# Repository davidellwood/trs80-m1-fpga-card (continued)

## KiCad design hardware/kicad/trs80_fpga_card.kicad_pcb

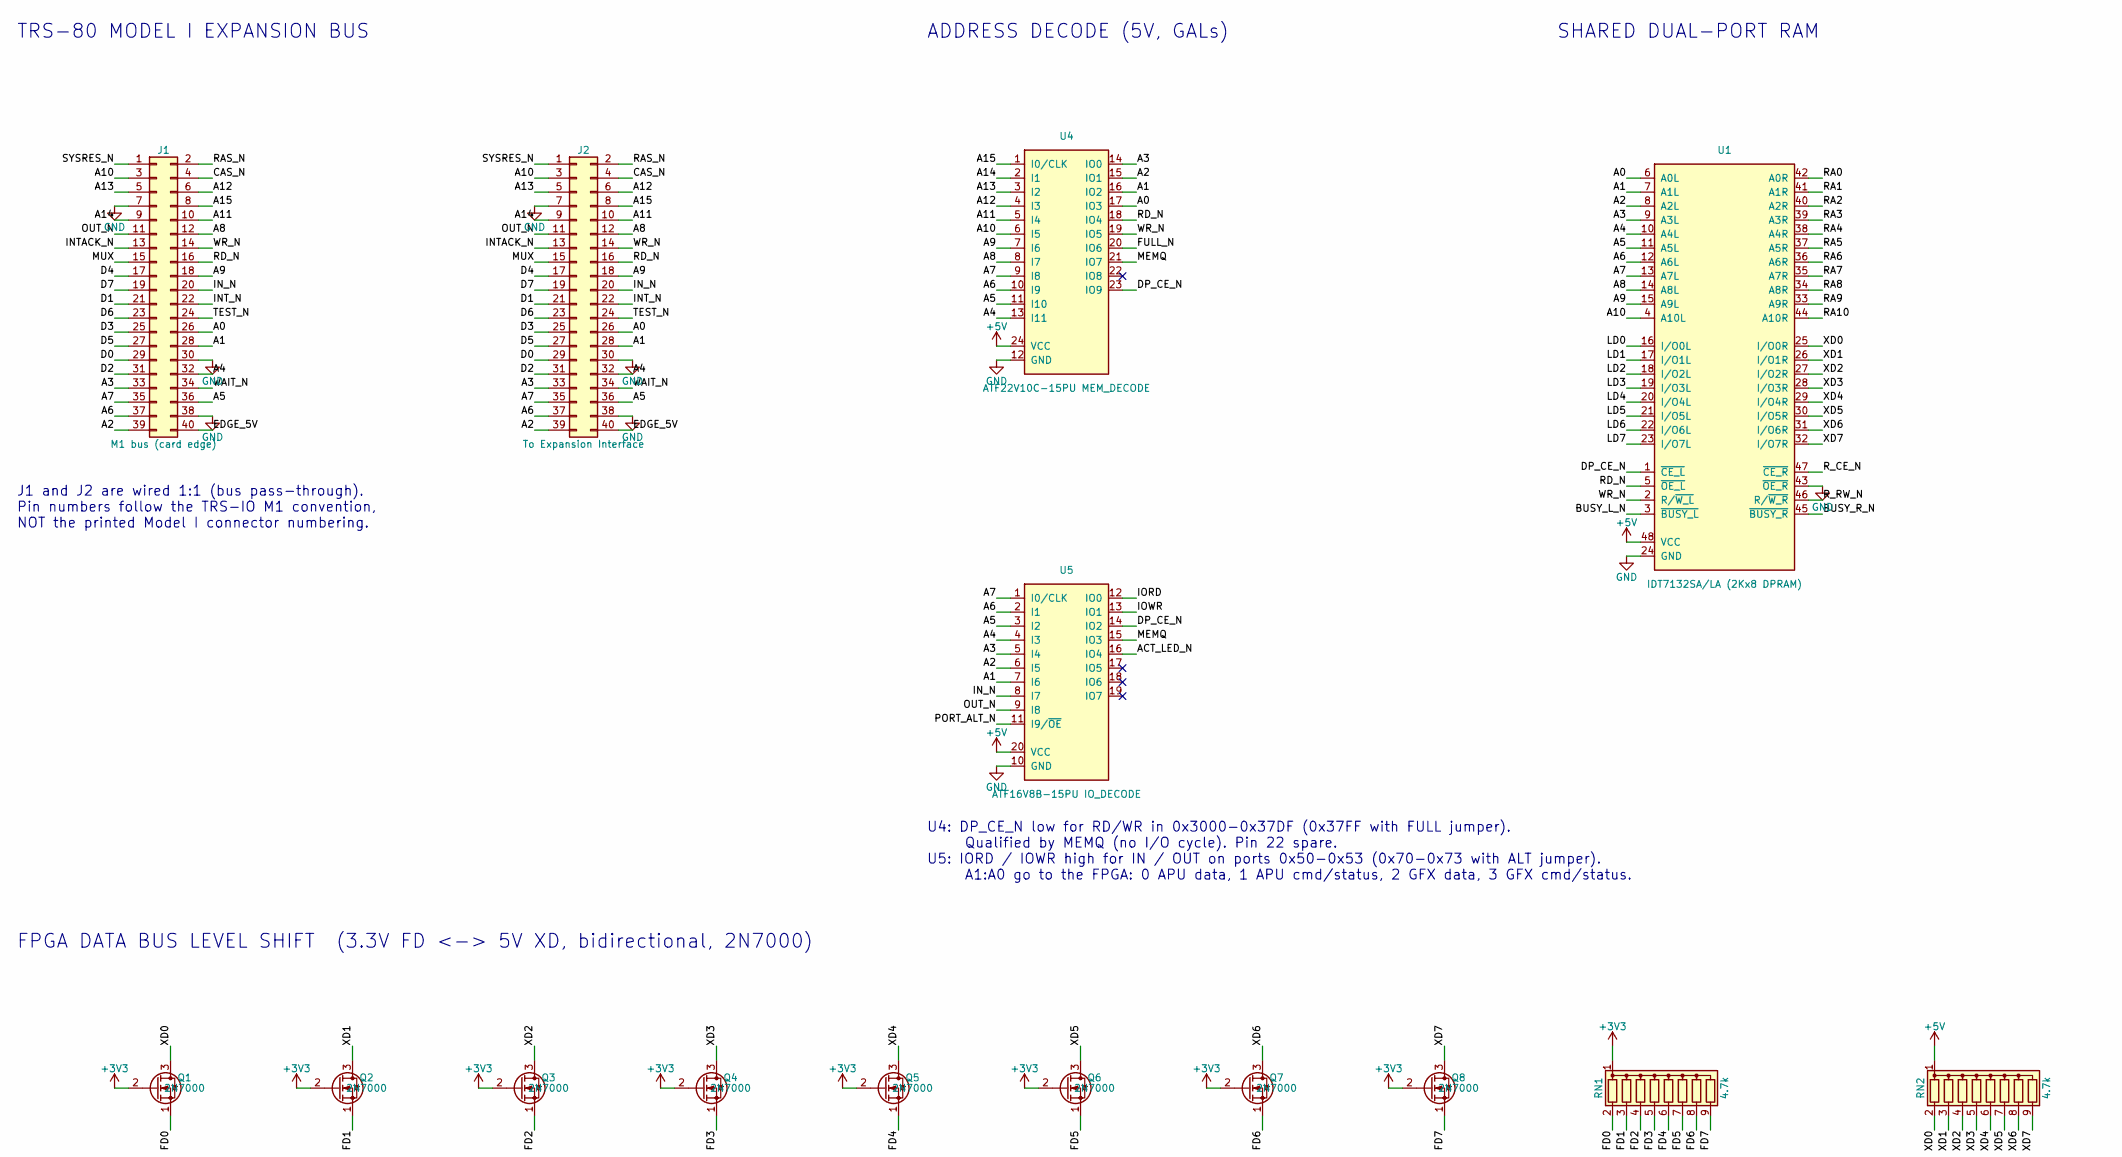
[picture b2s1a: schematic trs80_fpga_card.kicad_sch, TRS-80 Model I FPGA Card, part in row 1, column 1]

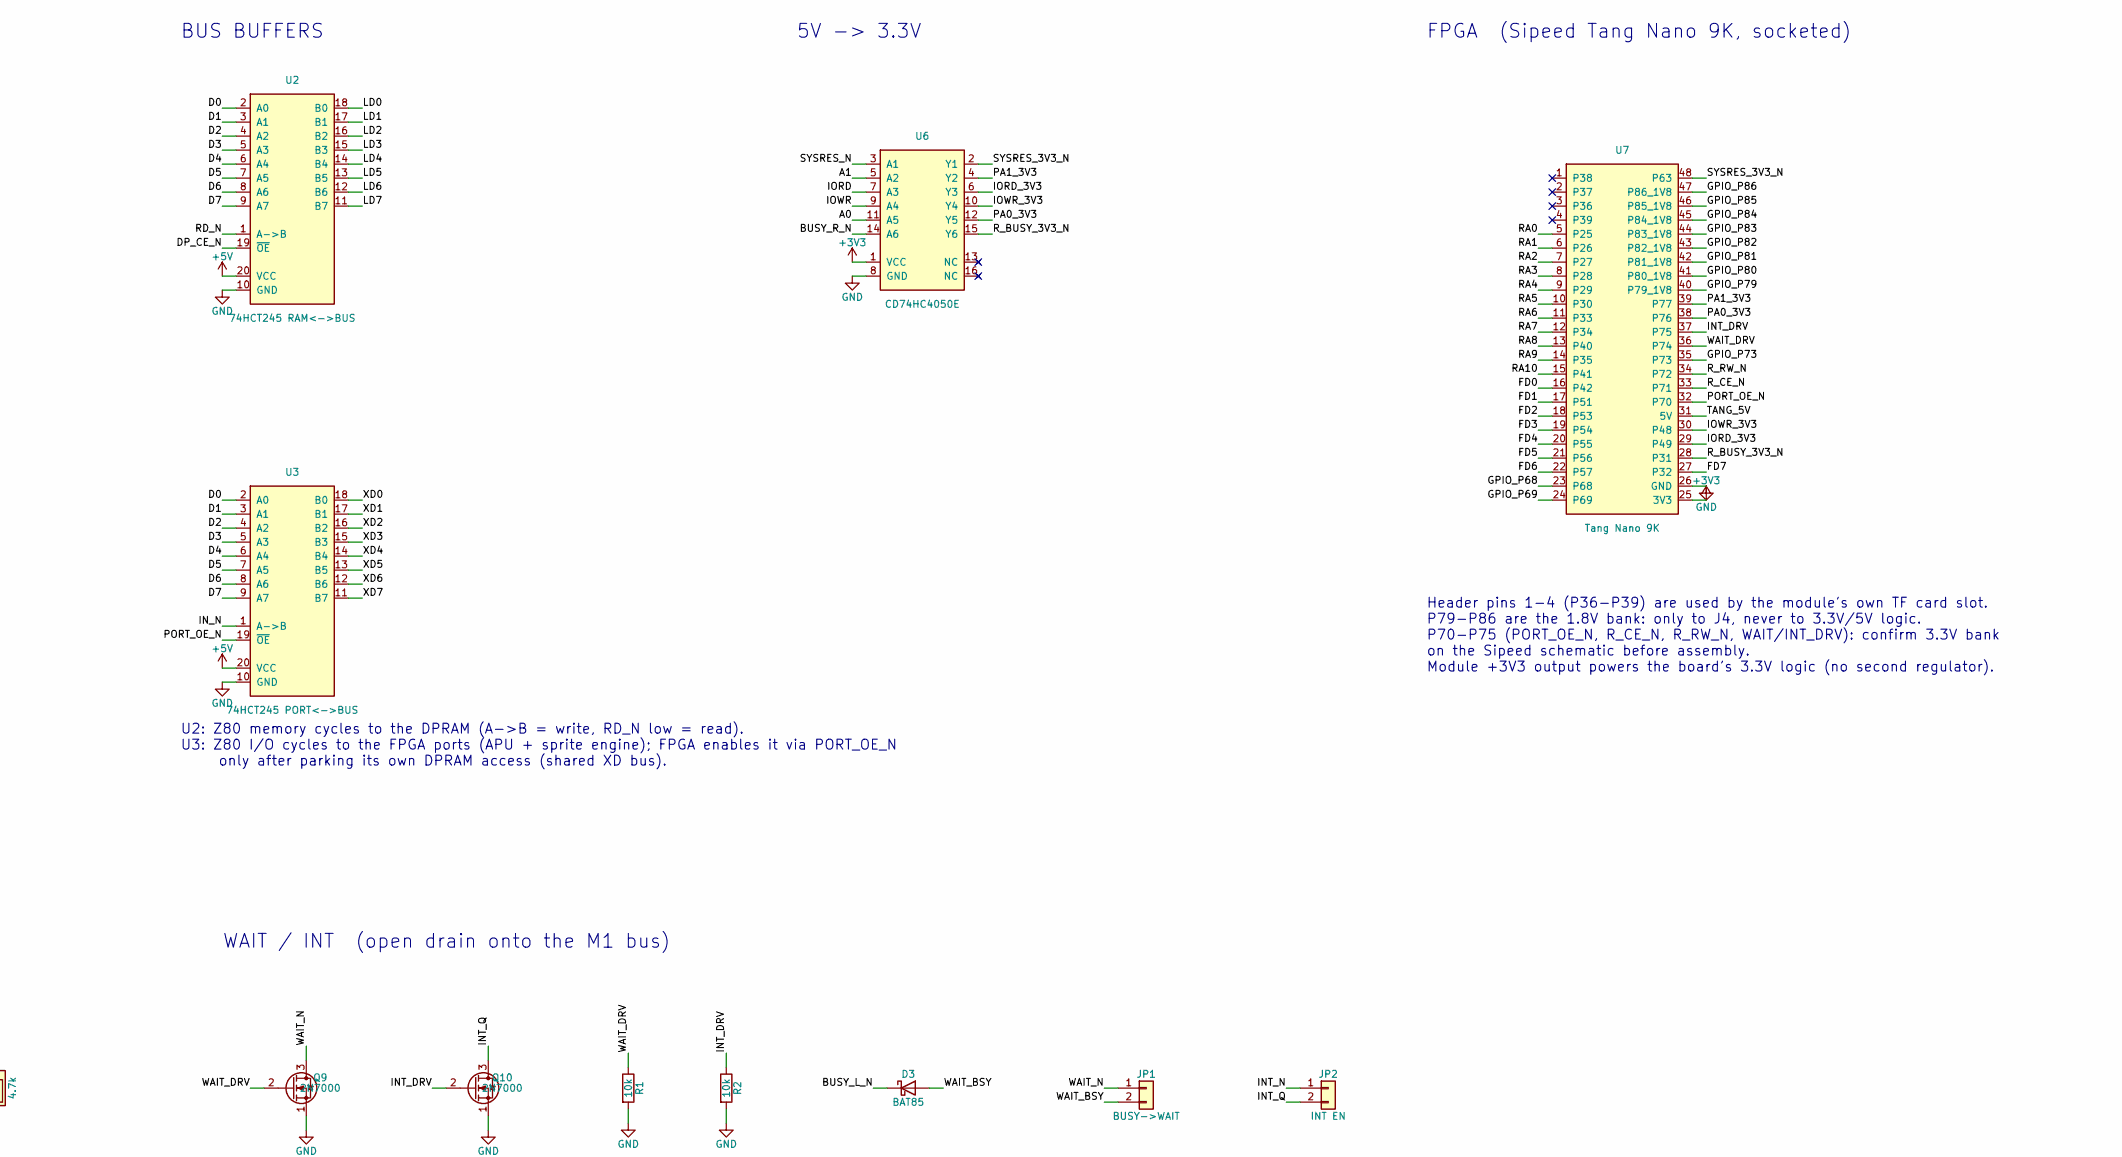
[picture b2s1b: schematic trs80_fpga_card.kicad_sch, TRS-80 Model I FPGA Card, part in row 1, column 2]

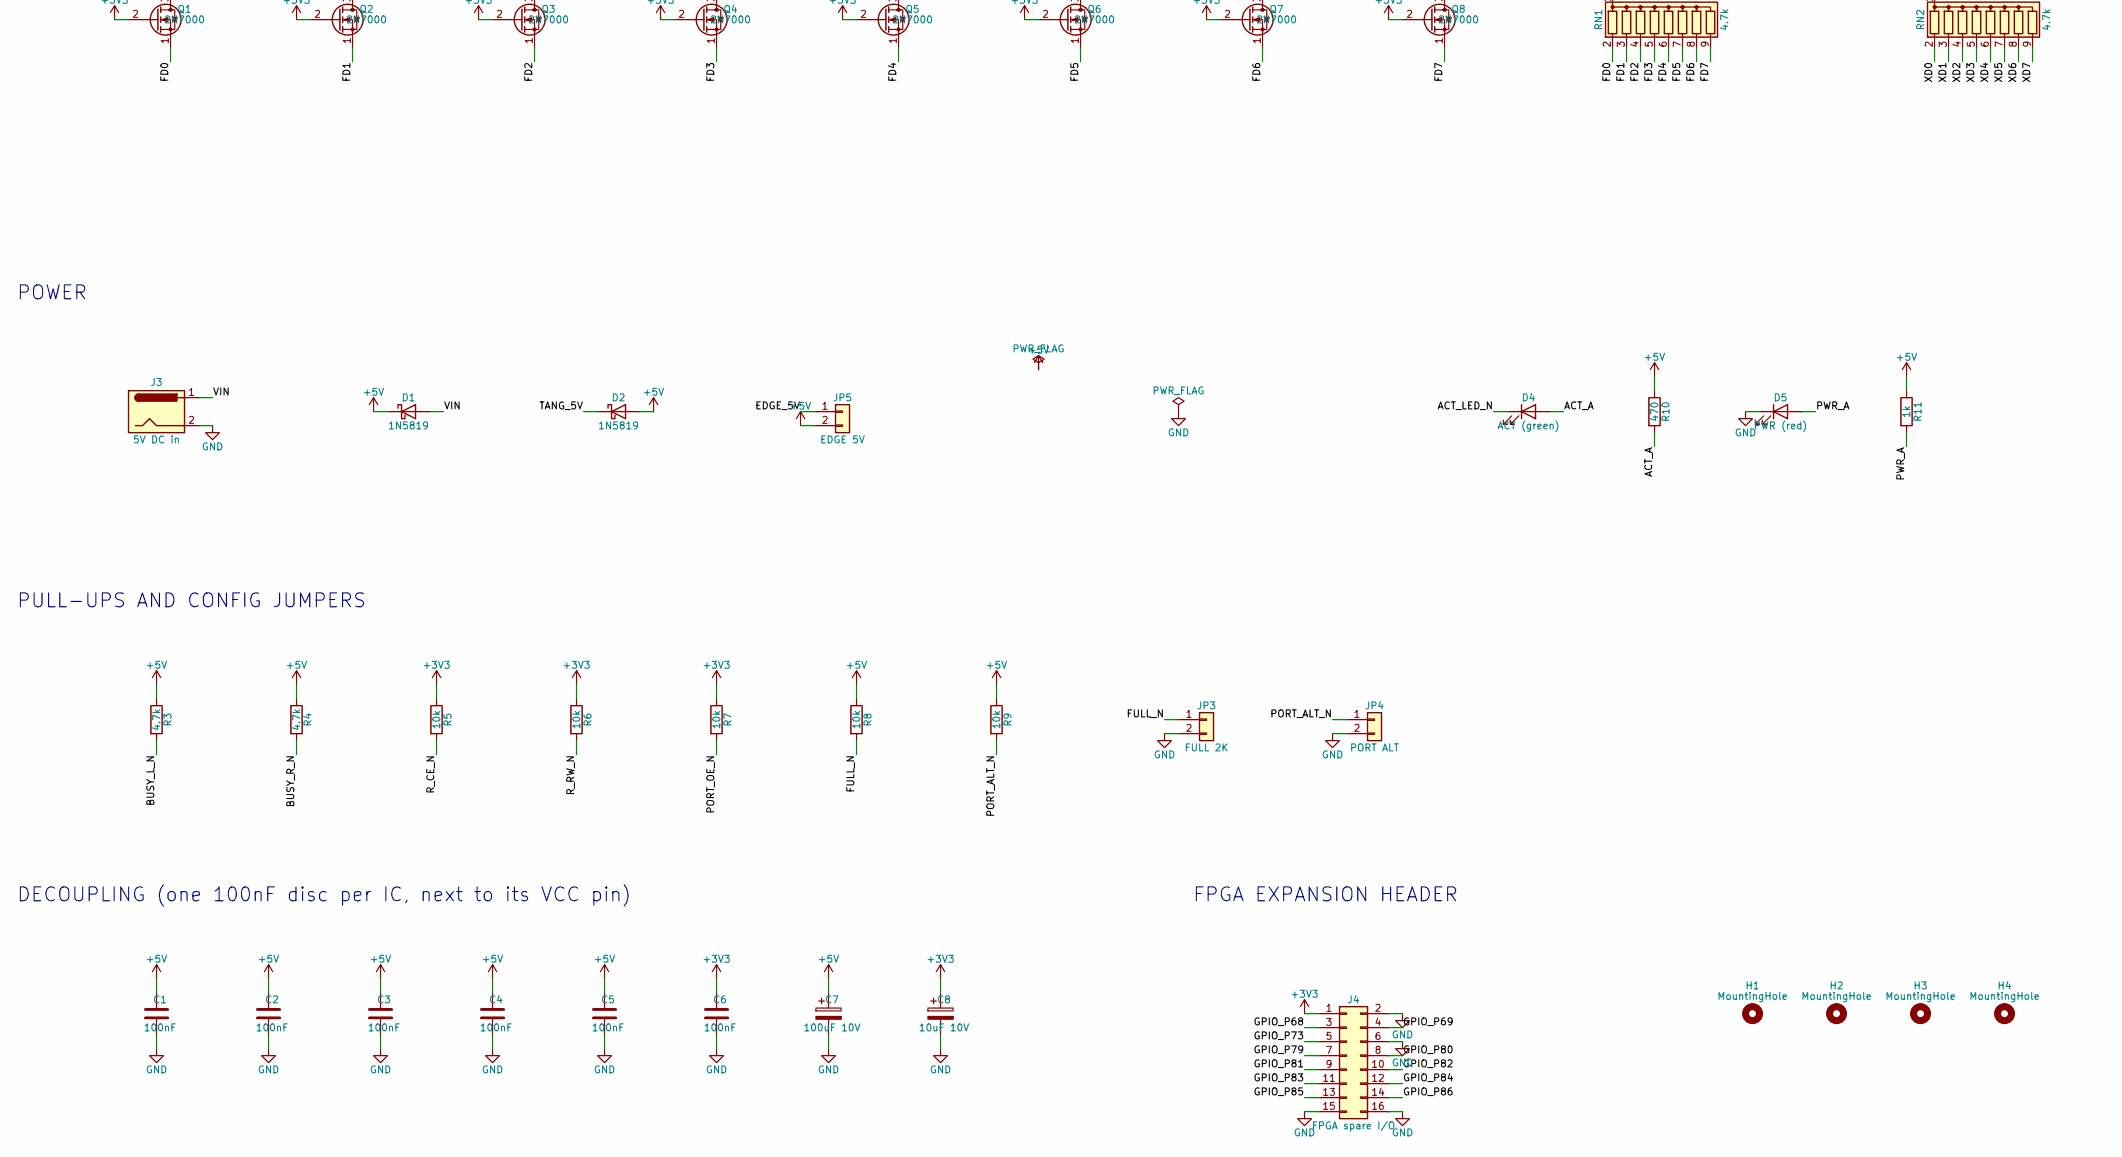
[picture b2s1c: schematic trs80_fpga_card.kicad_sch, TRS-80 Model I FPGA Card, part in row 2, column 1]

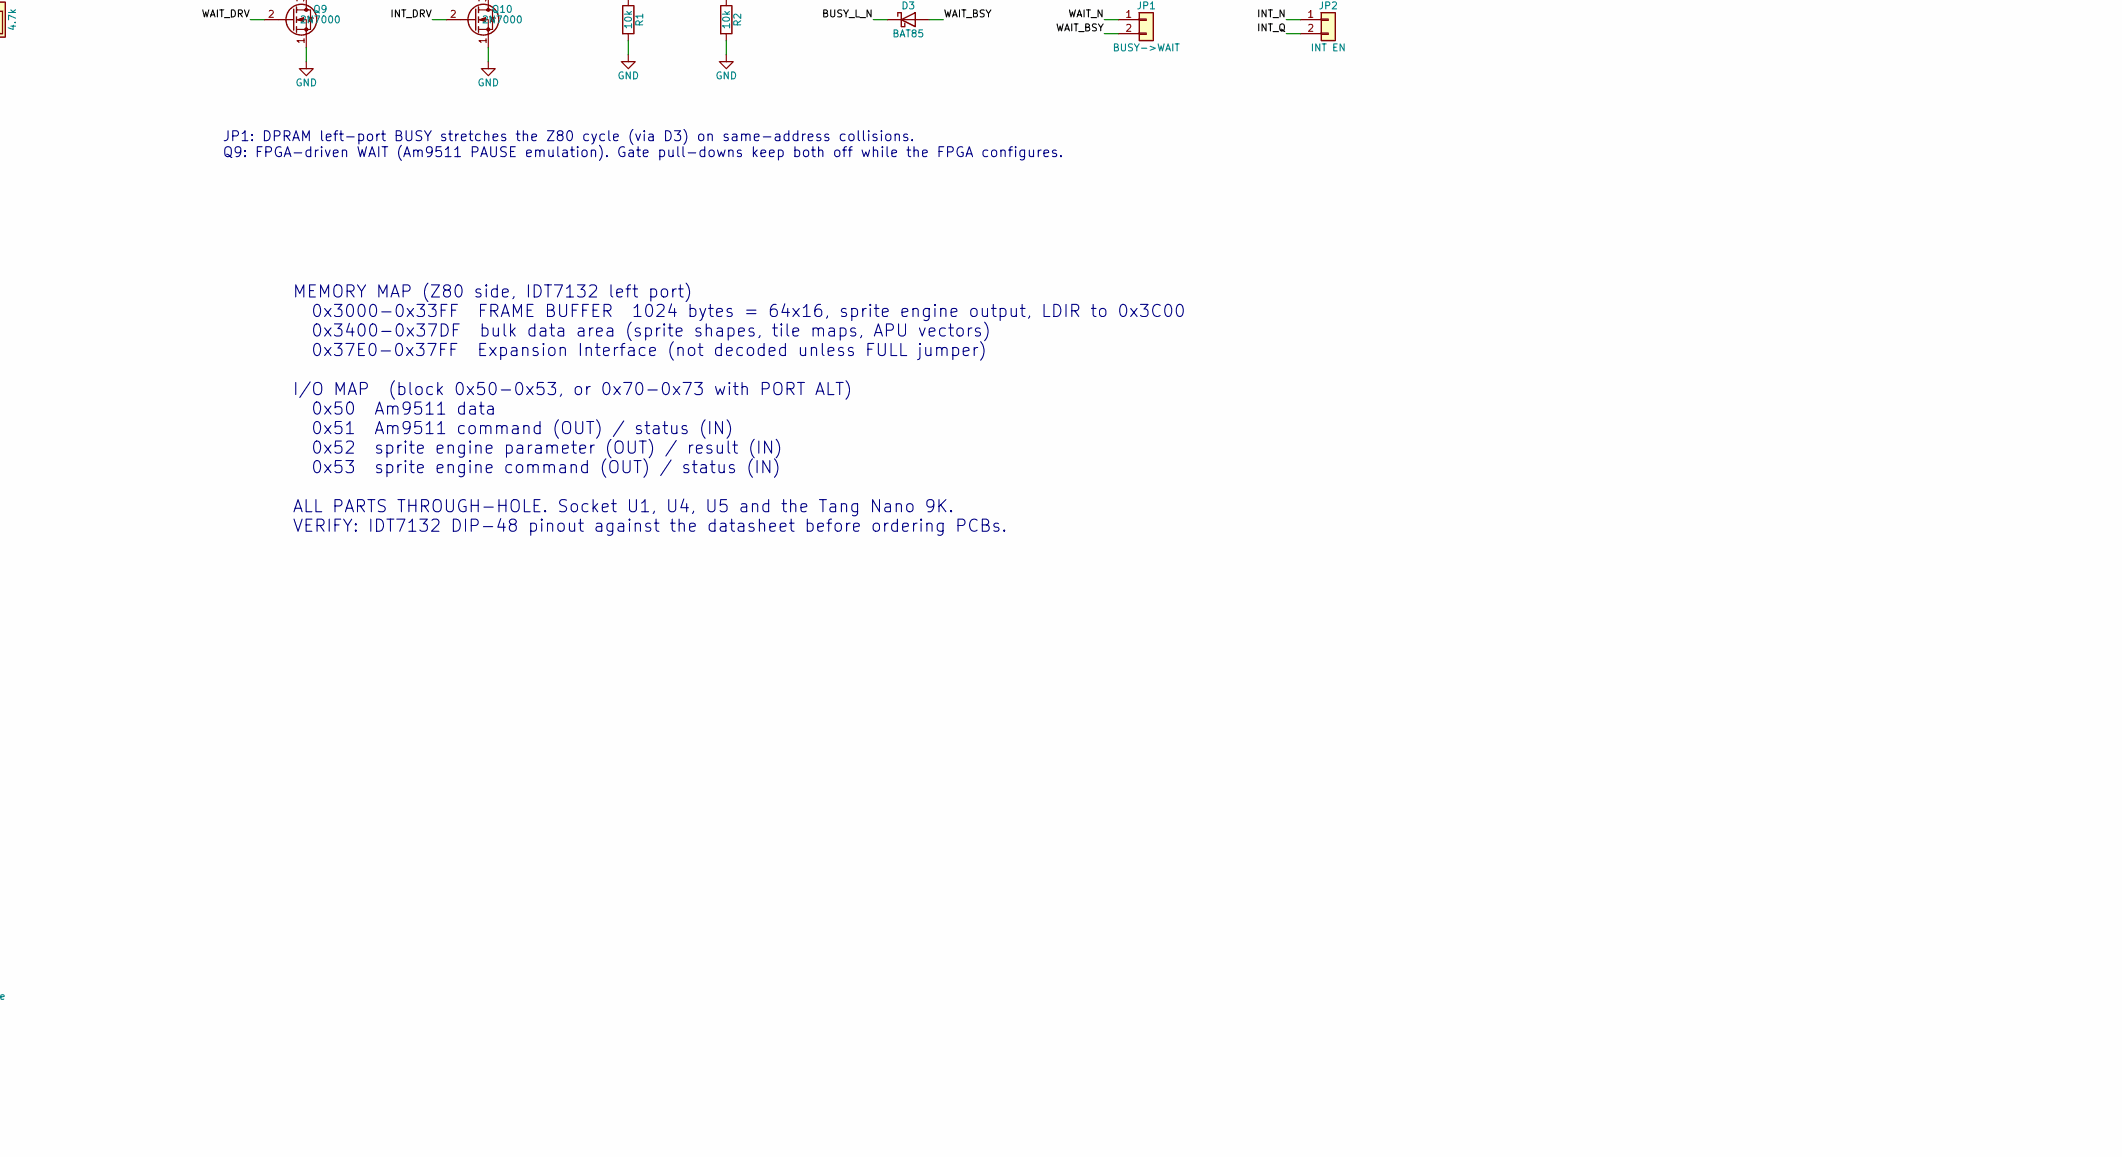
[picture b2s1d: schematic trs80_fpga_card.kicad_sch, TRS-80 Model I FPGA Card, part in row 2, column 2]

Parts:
C1, C2, C3, C4, C5, C6: 100nF; C_Disc_D5.0mm_W2.5mm_P5.00mm
C7: 100uF 10V; CP_Radial_D6.3mm_P2.50mm
C8: 10uF 10V; CP_Radial_D6.3mm_P2.50mm
D1, D2: 1N5819; D_DO-41_SOD81_P10.16mm_Horizontal
D3: BAT85; D_DO-35_SOD27_P7.62mm_Horizontal
D4: ACT (green); LED_D3.0mm
D5: PWR (red); LED_D3.0mm
H1, H2, H3, H4: MountingHole; MountingHole_3.2mm_M3
J1: M1 bus (card edge); TRS80_M1_Edge_40
J2: To Expansion Interface; IDC-Header_2x20_P2.54mm_Vertical
J3: 5V DC in; BarrelJack_Horizontal
J4: FPGA spare I/O; PinHeader_2x08_P2.54mm_Vertical
JP1: BUSY->WAIT; PinHeader_1x02_P2.54mm_Vertical
JP2: INT EN; PinHeader_1x02_P2.54mm_Vertical
JP3: FULL 2K; PinHeader_1x02_P2.54mm_Vertical
JP4: PORT ALT; PinHeader_1x02_P2.54mm_Vertical
JP5: EDGE 5V; PinHeader_1x02_P2.54mm_Vertical
Q1, Q2, Q3, Q4, Q5, Q6, Q7, Q8, Q9, Q10: 2N7000; TO-92_Inline_Wide
R1, R2, R5, R6, R7, R8, R9: 10k; R_Axial_DIN0207_L6.3mm_D2.5mm_P10.16mm_Horizontal
R3, R4: 4.7k; R_Axial_DIN0207_L6.3mm_D2.5mm_P10.16mm_Horizontal
R10: 470; R_Axial_DIN0207_L6.3mm_D2.5mm_P10.16mm_Horizontal
R11: 1k; R_Axial_DIN0207_L6.3mm_D2.5mm_P10.16mm_Horizontal
RN1, RN2: 4.7k; R_Array_SIP9
U1: IDT7132SA/LA (2Kx8 DPRAM); DIP-48_W15.24mm_Socket
U2: 74HCT245 RAM<->BUS; DIP-20_W7.62mm
U3: 74HCT245 PORT<->BUS; DIP-20_W7.62mm
U4: ATF22V10C-15PU MEM_DECODE; DIP-24_W7.62mm_Socket
U5: ATF16V8B-15PU IO_DECODE; DIP-20_W7.62mm_Socket
U6: CD74HC4050E; DIP-16_W7.62mm
U7: Tang Nano 9K; TangNano9K_DIP48_W22.86mm

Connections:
+3V3: C6.1, C8.1, J4.1, Q1.2 (G), Q2.2 (G), Q3.2 (G), Q4.2 (G), Q5.2 (G), Q6.2 (G), Q7.2 (G), Q8.2 (G), R5.1, R6.1, R7.1, RN1.1 (common), U6.1 (VCC), U7.25 (3V3)
+5V: C1.1, C2.1, C3.1, C4.1, C5.1, C7.1, D1.1 (K), D2.2 (A), JP5.2, R3.1, R4.1, R8.1, R9.1, R10.1, R11.1, RN2.1 (common), U1.48 (VCC), U2.20 (VCC), U3.20 (VCC), U4.24 (VCC), U5.20 (VCC)
/A0: J1.26, J2.26, U1.6 (A0L), U4.17 (IO3), U6.11 (A5)
/A1: J1.28, J2.28, U1.7 (A1L), U4.16 (IO2), U5.7 (I6), U6.5 (A2)
/A2: J1.39, J2.39, U1.8 (A2L), U4.15 (IO1), U5.6 (I5)
/A3: J1.33, J2.33, U1.9 (A3L), U4.14 (IO0), U5.5 (I4)
/A4: J1.32, J2.32, U1.10 (A4L), U4.13 (I11), U5.4 (I3)
/A5: J1.36, J2.36, U1.11 (A5L), U4.11 (I10), U5.3 (I2)
/A6: J1.37, J2.37, U1.12 (A6L), U4.10 (I9), U5.2 (I1)
/A7: J1.35, J2.35, U1.13 (A7L), U4.9 (I8), U5.1 (I0/CLK)
/A8: J1.12, J2.12, U1.14 (A8L), U4.8 (I7)
/A9: J1.18, J2.18, U1.15 (A9L), U4.7 (I6)
/A10: J1.3, J2.3, U1.4 (A10L), U4.6 (I5)
/A11: J1.10, J2.10, U4.5 (I4)
/A12: J1.6, J2.6, U4.4 (I3)
/A13: J1.5, J2.5, U4.3 (I2)
/A14: J1.9, J2.9, U4.2 (I1)
/A15: J1.8, J2.8, U4.1 (I0/CLK)
/ACT_A: D4.2 (A), R10.2
/ACT_LED_N: D4.1 (K), U5.16 (IO4)
/BUSY_L_N: D3.1 (K), R3.2, U1.3 (~BUSY_L)
/BUSY_R_N: R4.2, U1.45 (~BUSY_R), U6.14 (A6)
/CAS_N: J1.4, J2.4
/D0: J1.29, J2.29, U2.2 (A0), U3.2 (A0)
/D1: J1.21, J2.21, U2.3 (A1), U3.3 (A1)
/D2: J1.31, J2.31, U2.4 (A2), U3.4 (A2)
/D3: J1.25, J2.25, U2.5 (A3), U3.5 (A3)
/D4: J1.17, J2.17, U2.6 (A4), U3.6 (A4)
/D5: J1.27, J2.27, U2.7 (A5), U3.7 (A5)
/D6: J1.23, J2.23, U2.8 (A6), U3.8 (A6)
/D7: J1.19, J2.19, U2.9 (A7), U3.9 (A7)
/DP_CE_N: U1.1 (~CE_L), U2.19 (~OE), U4.23 (IO9), U5.14 (IO2)
/EDGE_5V: J1.40, J2.40, JP5.1
/FD0: Q1.1 (S), RN1.2 (R1), U7.16 (P42)
/FD1: Q2.1 (S), RN1.3 (R2), U7.17 (P51)
/FD2: Q3.1 (S), RN1.4 (R3), U7.18 (P53)
/FD3: Q4.1 (S), RN1.5 (R4), U7.19 (P54)
/FD4: Q5.1 (S), RN1.6 (R5), U7.20 (P55)
/FD5: Q6.1 (S), RN1.7 (R6), U7.21 (P56)
/FD6: Q7.1 (S), RN1.8 (R7), U7.22 (P57)
/FD7: Q8.1 (S), RN1.9 (R8), U7.27 (P32)
/FULL_N: JP3.1, R8.2, U4.20 (IO6)
/GPIO_P68: J4.3, U7.23 (P68)
/GPIO_P69: J4.4, U7.24 (P69)
/GPIO_P73: J4.5, U7.35 (P73)
/GPIO_P79: J4.7, U7.40 (P79_1V8)
/GPIO_P80: J4.8, U7.41 (P80_1V8)
/GPIO_P81: J4.9, U7.42 (P81_1V8)
/GPIO_P82: J4.10, U7.43 (P82_1V8)
/GPIO_P83: J4.11, U7.44 (P83_1V8)
/GPIO_P84: J4.12, U7.45 (P84_1V8)
/GPIO_P85: J4.13, U7.46 (P85_1V8)
/GPIO_P86: J4.14, U7.47 (P86_1V8)
/INTACK_N: J1.13, J2.13
/INT_DRV: Q10.2 (G), R2.1, U7.37 (P75)
/INT_N: J1.22, J2.22, JP2.1
/INT_Q: JP2.2, Q10.3 (D)
/IN_N: J1.20, J2.20, U3.1 (A->B), U5.8 (I7)
/IORD: U5.12 (IO0), U6.7 (A3)
/IORD_3V3: U6.6 (Y3), U7.29 (P49)
/IOWR: U5.13 (IO1), U6.9 (A4)
/IOWR_3V3: U6.10 (Y4), U7.30 (P48)
/LD0: U1.16 (I/O0L), U2.18 (B0)
/LD1: U1.17 (I/O1L), U2.17 (B1)
/LD2: U1.18 (I/O2L), U2.16 (B2)
/LD3: U1.19 (I/O3L), U2.15 (B3)
/LD4: U1.20 (I/O4L), U2.14 (B4)
/LD5: U1.21 (I/O5L), U2.13 (B5)
/LD6: U1.22 (I/O6L), U2.12 (B6)
/LD7: U1.23 (I/O7L), U2.11 (B7)
/MEMQ: U4.21 (IO7), U5.15 (IO3)
/MUX: J1.15, J2.15
/OUT_N: J1.11, J2.11, U5.9 (I8)
/PA0_3V3: U6.12 (Y5), U7.38 (P76)
/PA1_3V3: U6.4 (Y2), U7.39 (P77)
/PORT_ALT_N: JP4.1, R9.2, U5.11 (I9/~OE)
/PORT_OE_N: R7.2, U3.19 (~OE), U7.32 (P70)
/PWR_A: D5.2 (A), R11.2
/RA0: U1.42 (A0R), U7.5 (P25)
/RA1: U1.41 (A1R), U7.6 (P26)
/RA2: U1.40 (A2R), U7.7 (P27)
/RA3: U1.39 (A3R), U7.8 (P28)
/RA4: U1.38 (A4R), U7.9 (P29)
/RA5: U1.37 (A5R), U7.10 (P30)
/RA6: U1.36 (A6R), U7.11 (P33)
/RA7: U1.35 (A7R), U7.12 (P34)
/RA8: U1.34 (A8R), U7.13 (P40)
/RA9: U1.33 (A9R), U7.14 (P35)
/RA10: U1.44 (A10R), U7.15 (P41)
/RAS_N: J1.2, J2.2
/RD_N: J1.16, J2.16, U1.5 (~OE_L), U2.1 (A->B), U4.18 (IO4)
/R_BUSY_3V3_N: U6.15 (Y6), U7.28 (P31)
/R_CE_N: R5.2, U1.47 (~CE_R), U7.33 (P71)
/R_RW_N: R6.2, U1.46 (R/~W_R), U7.34 (P72)
/SYSRES_3V3_N: U6.2 (Y1), U7.48 (P63)
/SYSRES_N: J1.1, J2.1, U6.3 (A1)
/TANG_5V: D2.1 (K), U7.31 (5V)
/TEST_N: J1.24, J2.24
/VIN: D1.2 (A), J3.1
/WAIT_BSY: D3.2 (A), JP1.2
/WAIT_DRV: Q9.2 (G), R1.1, U7.36 (P74)
/WAIT_N: J1.34, J2.34, JP1.1, Q9.3 (D)
/WR_N: J1.14, J2.14, U1.2 (R/~W_L), U4.19 (IO5)
/XD0: Q1.3 (D), RN2.2 (R1), U1.25 (I/O0R), U3.18 (B0)
/XD1: Q2.3 (D), RN2.3 (R2), U1.26 (I/O1R), U3.17 (B1)
/XD2: Q3.3 (D), RN2.4 (R3), U1.27 (I/O2R), U3.16 (B2)
/XD3: Q4.3 (D), RN2.5 (R4), U1.28 (I/O3R), U3.15 (B3)
/XD4: Q5.3 (D), RN2.6 (R5), U1.29 (I/O4R), U3.14 (B4)
/XD5: Q6.3 (D), RN2.7 (R6), U1.30 (I/O5R), U3.13 (B5)
/XD6: Q7.3 (D), RN2.8 (R7), U1.31 (I/O6R), U3.12 (B6)
/XD7: Q8.3 (D), RN2.9 (R8), U1.32 (I/O7R), U3.11 (B7)
GND: C1.2, C2.2, C3.2, C4.2, C5.2, C6.2, C7.2, C8.2, D5.1 (K), J1.7, J1.30, J1.38, J2.7, J2.30, J2.38, J3.2, J4.2, J4.6, J4.15, J4.16, JP3.2, JP4.2, Q9.1 (S), Q10.1 (S), R1.2, R2.2, U1.24 (GND), U1.43 (~OE_R), U2.10 (GND), U3.10 (GND), U4.12 (GND), U5.10 (GND), U6.8 (GND), U7.26 (GND)

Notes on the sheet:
TRS-80 MODEL I EXPANSION BUS
J1 and J2 are wired 1:1 (bus pass-through). Pin numbers follow the TRS-IO M1 convention, NOT the printed Model I connector numbering.
ADDRESS DECODE (5V, GALs)
U4: DP_CE_N low for RD/WR in 0x3000-0x37DF (0x37FF with FULL jumper). Qualified by MEMQ (no I/O cycle). Pin 22 spare. U5: IORD / IOWR high for IN / OUT on ports 0x50-0x53 (0x70-0x73 with ALT jumper). A1:A0 go to the FPGA: 0 APU data, 1 APU cmd/status, 2 GFX data, 3 GFX cmd/status.
SHARED DUAL-PORT RAM
BUS BUFFERS
U2: Z80 memory cycles to the DPRAM (A->B = write, RD_N low = read). U3: Z80 I/O cycles to the FPGA ports (APU + sprite engine); FPGA enables it via PORT_OE_N only after parking its own DPRAM access (shared XD bus).
5V -> 3.3V
FPGA (Sipeed Tang Nano 9K, socketed)
Header pins 1-4 (P36-P39) are used by the module's own TF card slot. P79-P86 are the 1.8V bank: only to J4, never to 3.3V/5V logic. P70-P75 (PORT_OE_N, R_CE_N, R_RW_N, WAIT/INT_DRV): confirm 3.3V bank on the Sipeed schematic before assembly. Module +3V3 output powers the board's 3.3V logic (no seco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
FPGA DATA BUS LEVEL SHIFT (3.3V FD <-> 5V XD, bidirectional, 2N7000)
WAIT / INT (open drain onto the M1 bus)
JP1: DPRAM left-port BUSY stretches the Z80 cycle (via D3) on same-address collisions. Q9: FPGA-driven WAIT (Am9511 PAUSE emulation). Gate pull-downs keep both off while the FPGA configures.
POWER
PULL-UPS AND CONFIG JUMPERS
DECOUPLING (one 100nF disc per IC, next to its VCC pin)
FPGA EXPANSION HEADER
MEMORY MAP (Z80 side, IDT7132 left port) 0x3000-0x33FF FRAME BUFFER 1024 bytes = 64x16, sprite engine output, LDIR to 0x3C00 0x3400-0x37DF bulk data area (sprite shapes, tile maps, APU vectors) 0x37E0-0x37FF Expansion Interface (not decoded unless FULL jumper) I/O MAP (block 0x50-0x53, or 0x70-0x73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

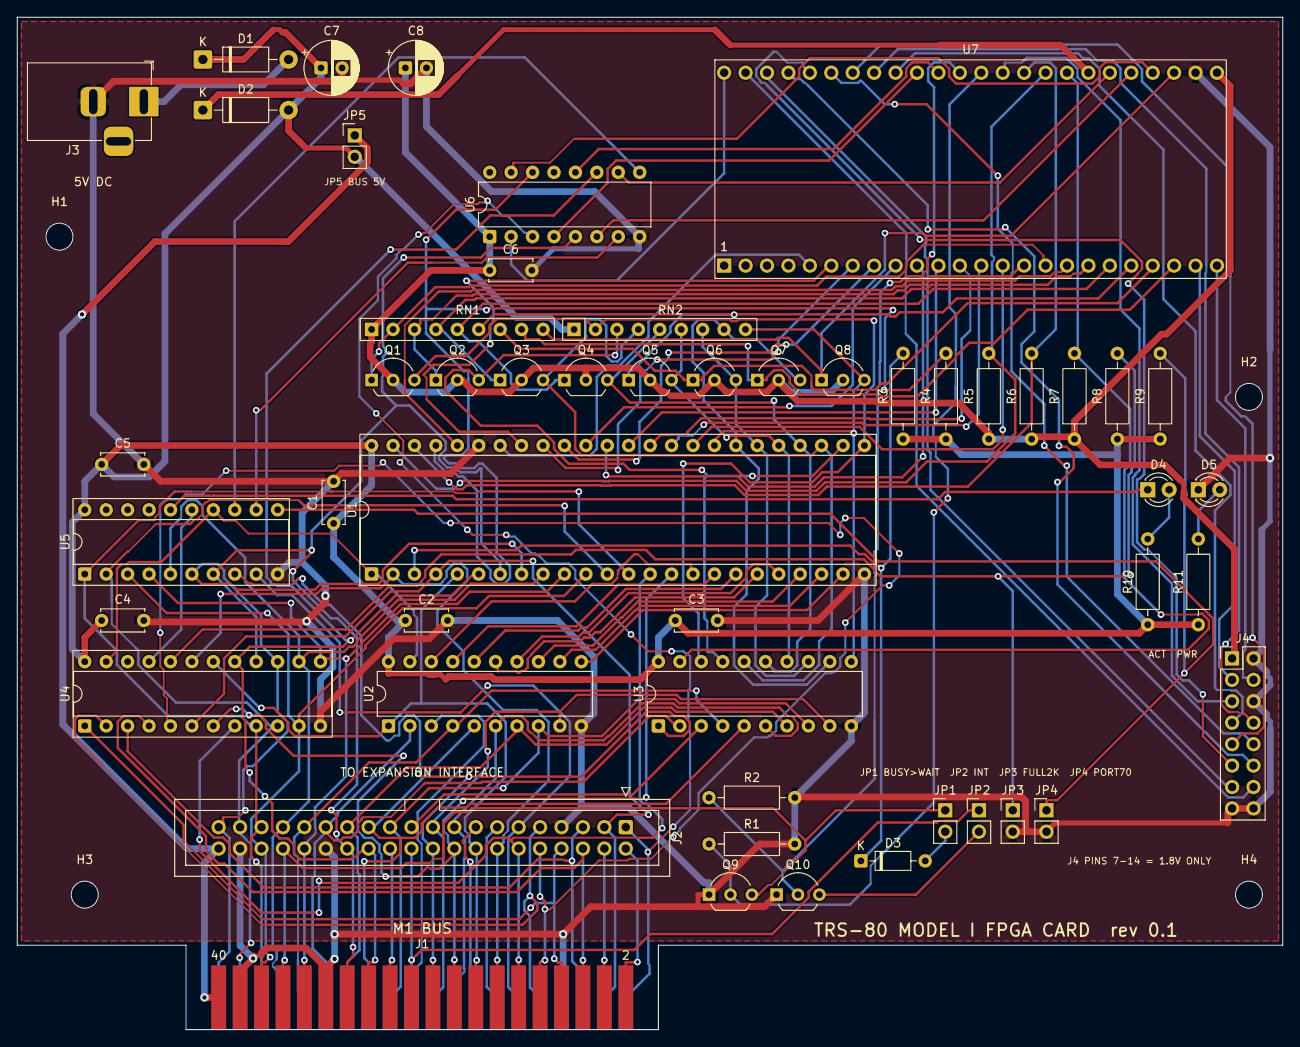
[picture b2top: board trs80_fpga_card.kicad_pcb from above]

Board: 2 copper layers, 150.0 x 120.0 mm, 56 parts (0 on the bottom side), 112 nets.
